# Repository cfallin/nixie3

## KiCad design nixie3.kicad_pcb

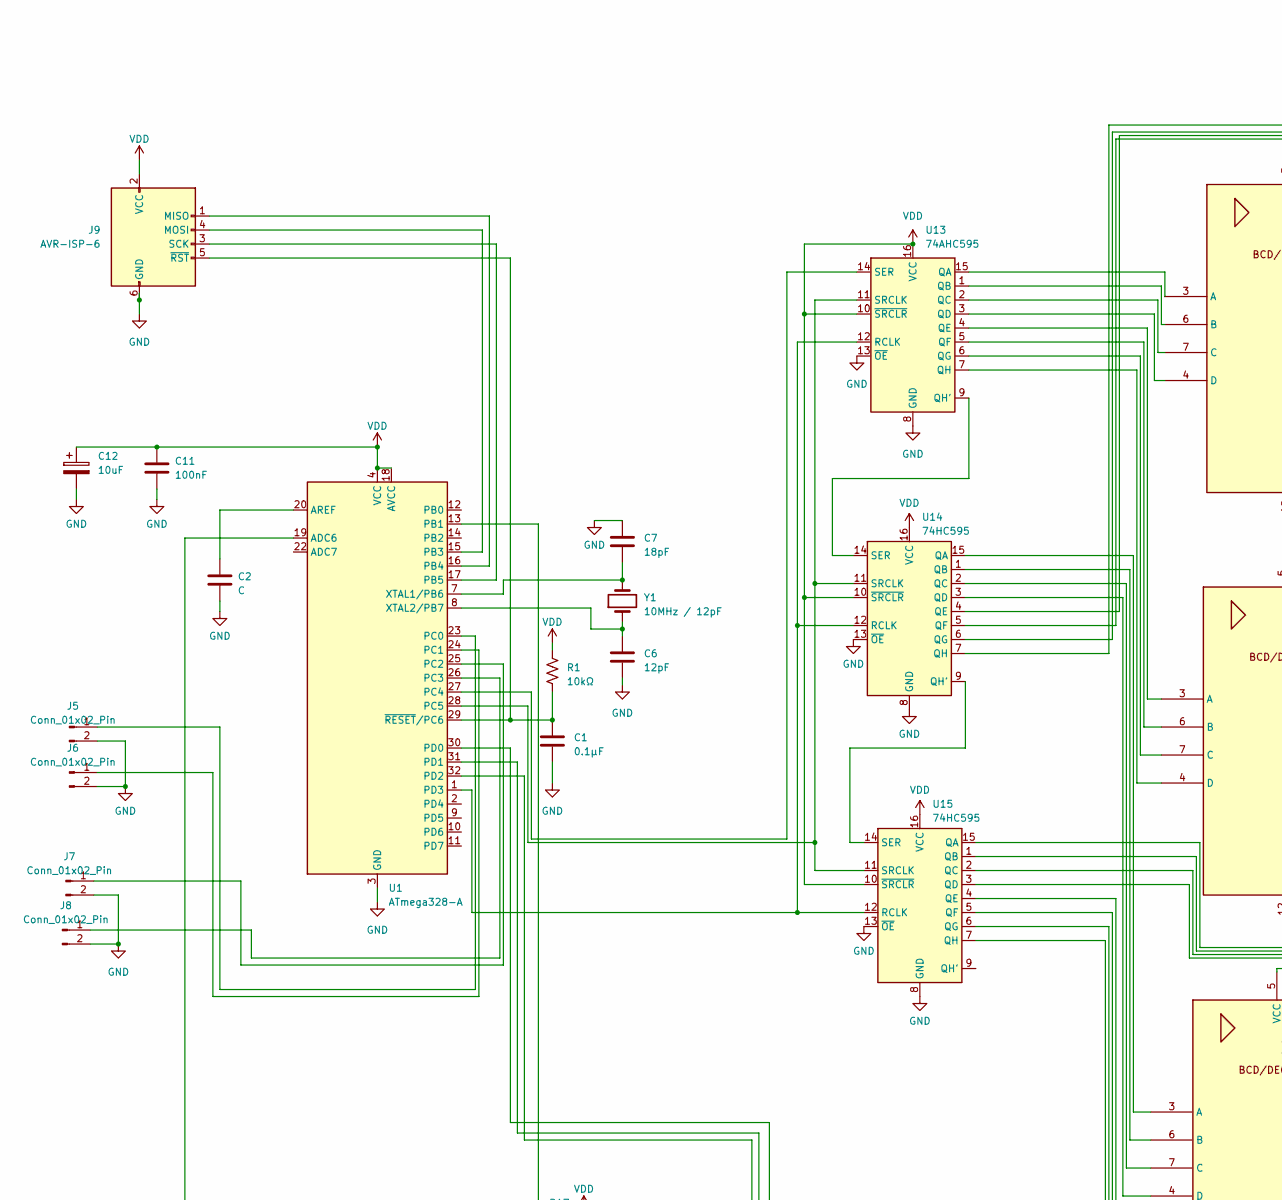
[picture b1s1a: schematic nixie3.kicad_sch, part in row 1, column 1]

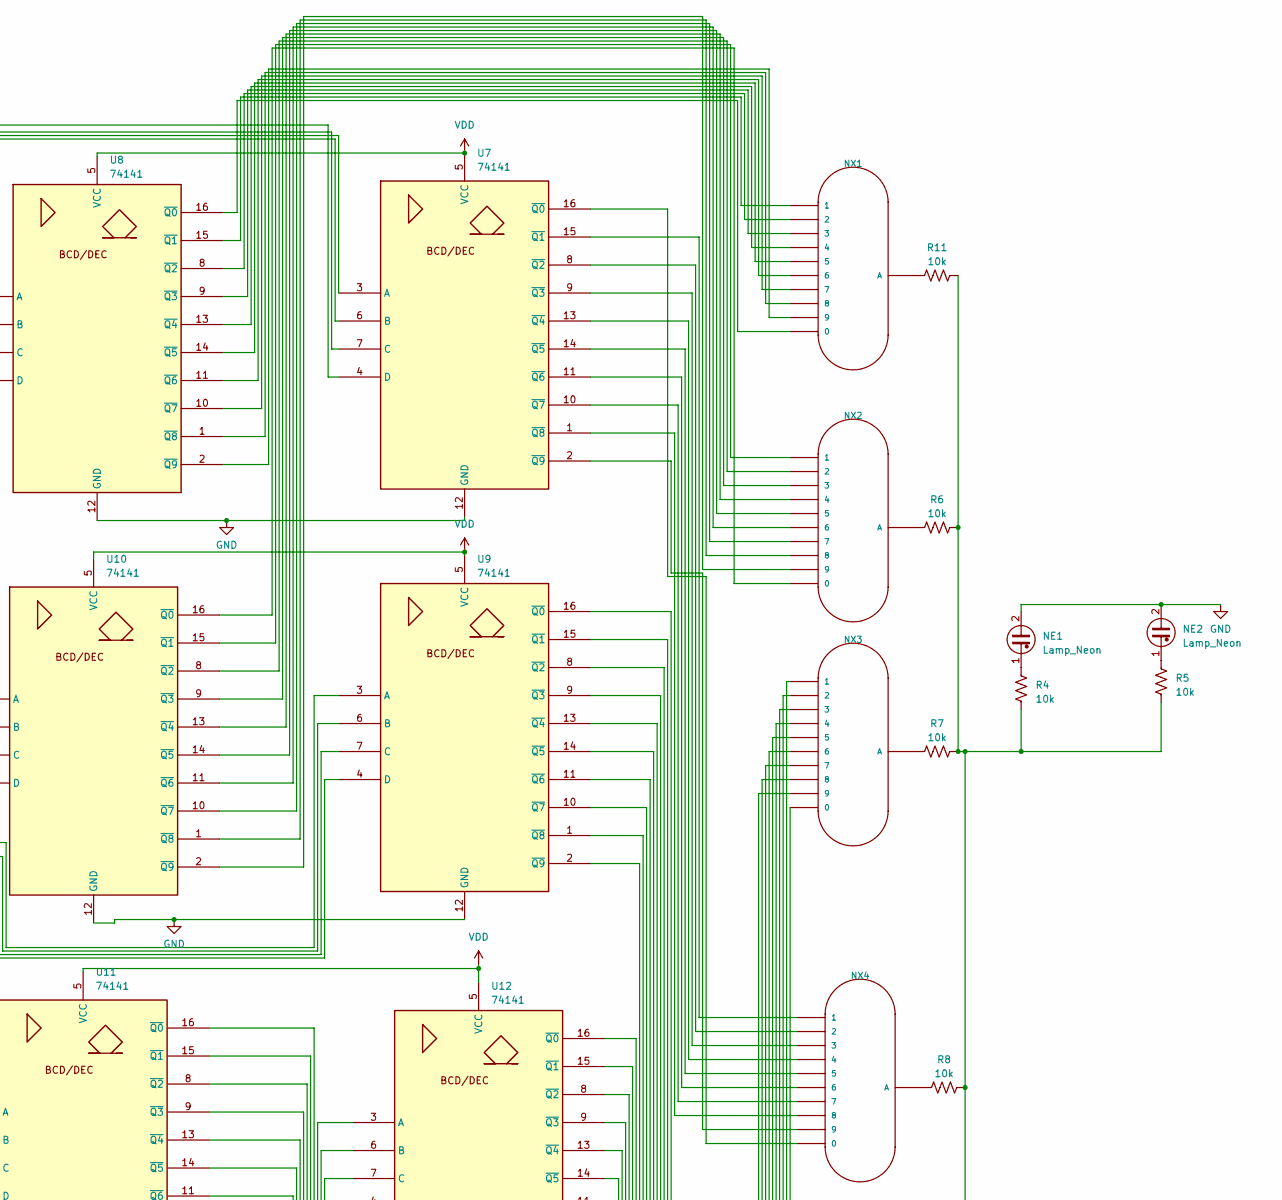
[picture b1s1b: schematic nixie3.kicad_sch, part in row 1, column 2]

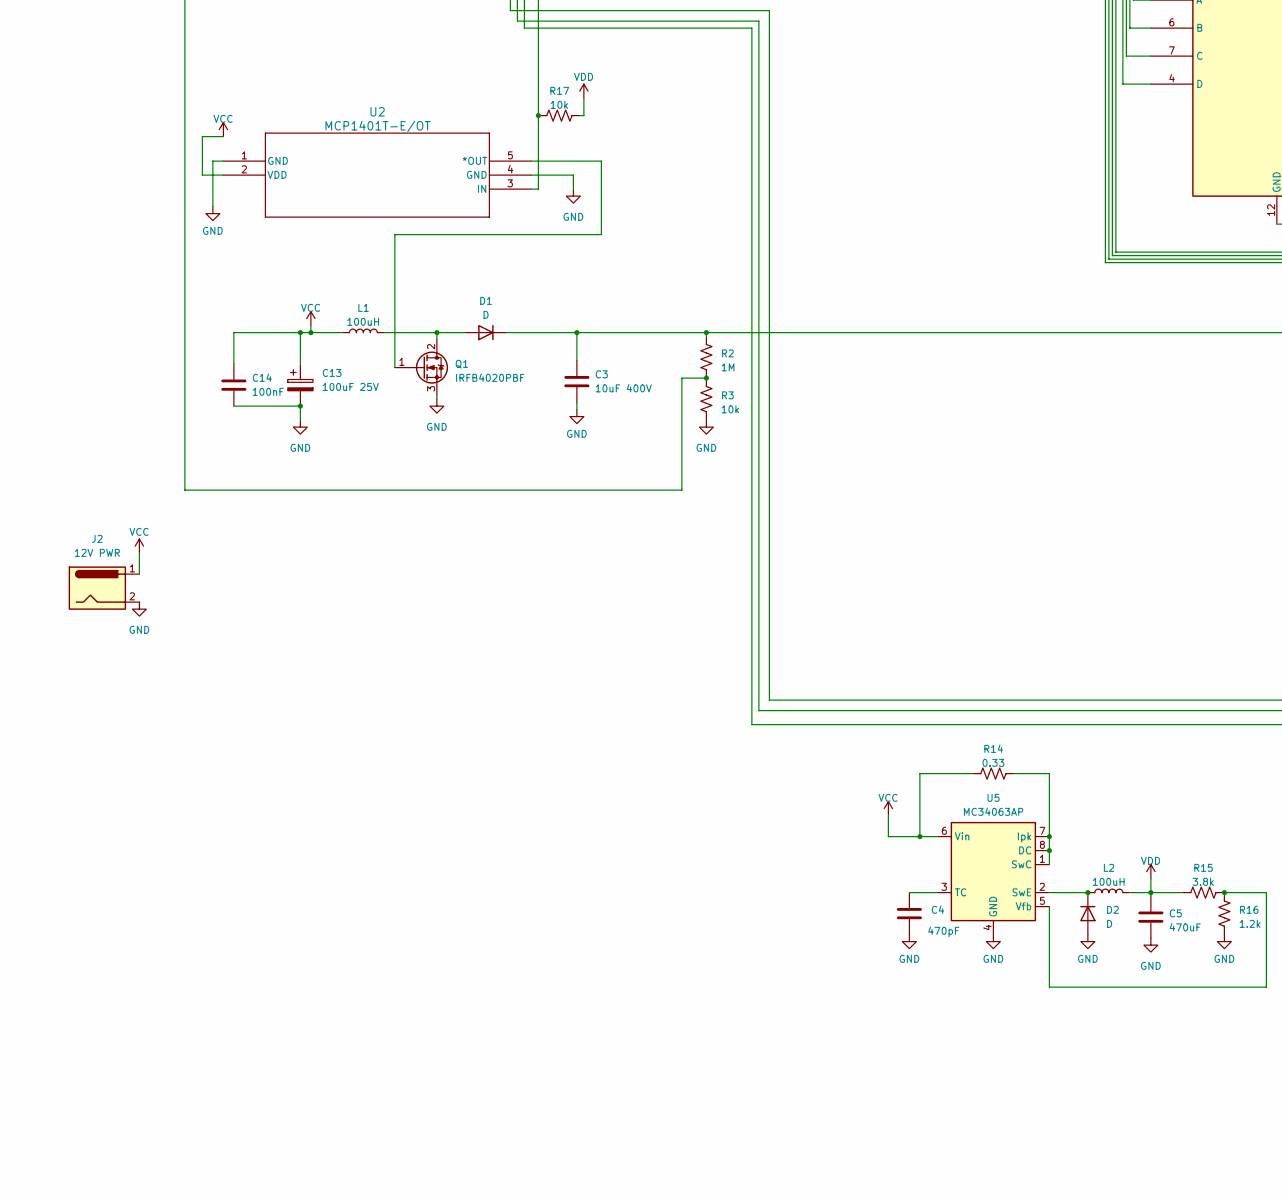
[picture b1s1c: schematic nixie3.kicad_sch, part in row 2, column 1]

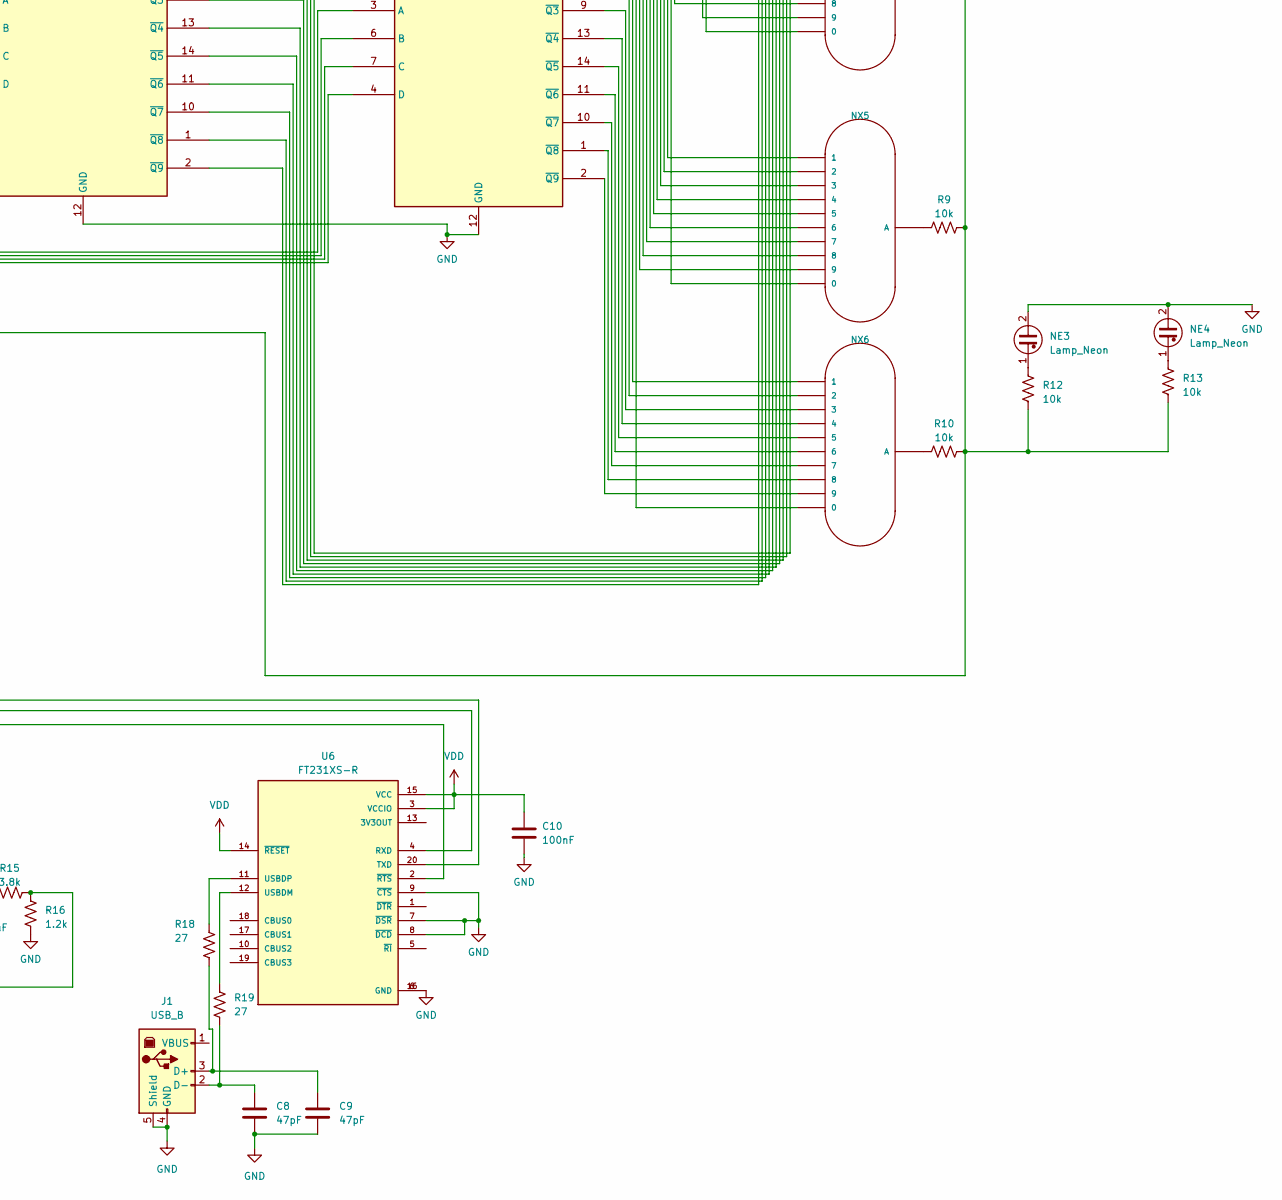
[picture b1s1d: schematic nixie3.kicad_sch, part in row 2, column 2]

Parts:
C1: 0.1µF; CP_Radial_D4.0mm_P1.50mm
C2: C; CP_Radial_D4.0mm_P1.50mm
C3: 10uF 400V; CP_Radial_D8.0mm_P5.00mm
C4: 470pF; C_Disc_D6.0mm_W2.5mm_P5.00mm
C5: 470uF; CP_Radial_D8.0mm_P5.00mm
C6: 12pF; C_Disc_D5.0mm_W2.5mm_P5.00mm
C7: 18pF; C_Disc_D5.0mm_W2.5mm_P5.00mm
C8, C9: 47pF; CP_Radial_D5.0mm_P2.50mm
C10, C11, C14: 100nF; CP_Radial_D5.0mm_P2.50mm
C12: 10uF; CP_Radial_D5.0mm_P2.50mm
C13: 100uF 25V; CP_Radial_D8.0mm_P5.00mm
D1, D2: D; D_DO-15_P12.70mm_Horizontal
J1: USB_B; USB_B_OST_USB-B1HSxx_Horizontal
J2: 12V PWR; BarrelJack_Horizontal
J5, J6, J7, J8: Conn_01x02_Pin; PinHeader_1x02_P2.54mm_Vertical
J9: AVR-ISP-6; PinHeader_2x03_P2.54mm_Vertical
L1, L2: 100uH; L_Toroid_Vertical_L16.0mm_W8.0mm_P7.62mm
NE1, NE2, NE3, NE4: Lamp_Neon; LED_D3.0mm
NX1, NX2, NX3, NX4, NX5, NX6: IN-12A; nixies-us-IN-12
Q1: IRFB4020PBF; TO-220-3_Vertical
R1: 10kΩ; R_Axial_DIN0204_L3.6mm_D1.6mm_P1.90mm_Vertical
R2: 1M; R_Axial_DIN0207_L6.3mm_D2.5mm_P2.54mm_Vertical
R3, R4, R5, R6, R7, R8, R9, R10, R11, R12, R13, R17: 10k; R_Axial_DIN0207_L6.3mm_D2.5mm_P2.54mm_Vertical
R14: 0.33; R_Axial_DIN0207_L6.3mm_D2.5mm_P2.54mm_Vertical
R15: 3.8k; R_Axial_DIN0207_L6.3mm_D2.5mm_P2.54mm_Vertical
R16: 1.2k; R_Axial_DIN0207_L6.3mm_D2.5mm_P2.54mm_Vertical
R18, R19: 27; R_Axial_DIN0204_L3.6mm_D1.6mm_P2.54mm_Vertical
U1: ATmega328-A; TQFP-32_7x7mm_P0.8mm
U2: MCP1401T-E/OT; SOT-23-5_MC_MCH
U5: MC34063AP; DIP-8_W7.62mm
U6: FT231XS-R; SOP63P599X175-20N; PARTREV 1.2; DigiKey_Part_Number 768-1129-2-ND
U7, U8, U9, U10, U11, U12: 74141; DIP-16_W7.62mm
U13: 74AHC595; DIP-16_W7.62mm
U14, U15: 74HC595; DIP-16_W7.62mm
Y1: 10MHz / 12pF; Crystal_HC49-U_Vertical

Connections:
GND: C1.2, C2.2, C3.2, C4.2, C5.2, C6.1, C7.1, C8.2, C9.2, C10.2, C11.2, C12.2, C13.2, C14.2, D2.2 (A), J1.4 (GND), J1.5 (Shield), J2.2, J5.2, J6.2, J7.2, J8.2, J9.6 (GND), NE1.2, NE2.2, NE3.2, NE4.2, Q1.3 (S), R3.2, R16.2, U1.3 (GND), U1.5 (GND), U1.21 (GND), U2.1 (GND), U2.4 (GND), U5.4 (GND), U6.6 (GND), U6.7 (~DSR), U6.8 (~DCD), U6.9 (~CTS), U6.16 (GND), U7.12 (GND), U8.12 (GND), U9.12 (GND), U10.12 (GND), U11.12 (GND), U12.12 (GND), U13.8 (GND), U13.13 (~OE), U14.8 (GND), U14.13 (~OE), U15.8 (GND), U15.13 (~OE)
unnamed: D1.2 (A), L1.2, Q1.2 (D)
unnamed: C3.1, D1.1 (K), R2.1, R4.1, R5.2, R6.2, R7.2, R8.2, R9.2, R10.2, R11.2, R12.2, R13.2
unnamed: D2.1 (K), L2.1, U5.2 (SwE)
unnamed: C9.1, J1.3 (D+), R18.2
unnamed: C8.1, J1.2 (D-), R19.2
unnamed: J5.1, U1.23 (PC0)
unnamed: J6.1, U1.24 (PC1)
unnamed: J7.1, U1.25 (PC2)
unnamed: J8.1, U1.26 (PC3)
unnamed: J9.1 (MISO), U1.16 (PB4)
unnamed: J9.4 (MOSI), U1.15 (PB3)
unnamed: J9.3 (SCK), U1.17 (PB5)
unnamed: C1.1, J9.5 (~RST), R1.2, U1.29 (~RESET/PC6)
unnamed: NE1.1, R4.2
unnamed: NE2.1, R5.1
unnamed: NE3.1, R12.1
unnamed: NE4.1, R13.1
unnamed: NX1.A, R11.1
unnamed: NX2.A, R6.1
unnamed: NX3.A, R7.1
unnamed: NX4.A, R8.1
unnamed: NX5.A, R9.1
unnamed: NX6.A, R10.1
unnamed: Q1.1 (G), U2.5 (*OUT)
unnamed: R2.2, R3.1, U1.19 (ADC6)
unnamed: C2.1, U1.20 (AREF)
unnamed: R17.1, U1.13 (PB1), U2.3 (IN)
unnamed: U1.27 (PC4), U13.14 (SER)
unnamed: U1.28 (PC5), U13.11 (SRCLK), U14.11 (SRCLK), U15.11 (SRCLK)
unnamed: U1.30 (PD0), U6.20 (TXD)
unnamed: U1.31 (PD1), U6.4 (RXD)
unnamed: U1.32 (PD2), U6.2 (~RTS)
unnamed: U1.1 (PD3), U13.12 (RCLK), U14.12 (RCLK), U15.12 (RCLK)
unnamed: C7.2, U1.7 (XTAL1/PB6), Y1.2
unnamed: C6.2, U1.8 (XTAL2/PB7), Y1.1
unnamed: R14.2, U5.1 (SwC), U5.7 (Ipk), U5.8 (DC)
unnamed: C4.1, U5.3 (TC)
unnamed: R15.2, R16.1, U5.5 (Vfb)
unnamed: R19.1, U6.12 (USBDM)
unnamed: R18.1, U6.11 (USBDP)
unnamed: NX4.0, U7.16 (~Q0)
unnamed: NX4.1, U7.15 (~Q1)
unnamed: NX4.2, U7.8 (~Q2)
unnamed: NX4.3, U7.9 (~Q3)
unnamed: NX4.4, U7.13 (~Q4)
unnamed: NX4.5, U7.14 (~Q5)
unnamed: NX4.6, U7.11 (~Q6)
unnamed: NX4.7, U7.10 (~Q7)
unnamed: NX4.8, U7.1 (~Q8)
unnamed: NX4.9, U7.2 (~Q9)
unnamed: NX1.0, U8.16 (~Q0)
unnamed: NX1.1, U8.15 (~Q1)
unnamed: NX1.2, U8.8 (~Q2)
unnamed: NX1.3, U8.9 (~Q3)
unnamed: NX1.4, U8.13 (~Q4)
unnamed: NX1.5, U8.14 (~Q5)
unnamed: NX1.6, U8.11 (~Q6)
unnamed: NX1.7, U8.10 (~Q7)
unnamed: NX1.8, U8.1 (~Q8)
unnamed: NX1.9, U8.2 (~Q9)
unnamed: NX5.0, U9.16 (~Q0)
unnamed: NX5.1, U9.15 (~Q1)
unnamed: NX5.2, U9.8 (~Q2)
unnamed: NX5.3, U9.9 (~Q3)
unnamed: NX5.4, U9.13 (~Q4)
unnamed: NX5.5, U9.14 (~Q5)
unnamed: NX5.6, U9.11 (~Q6)
unnamed: NX5.7, U9.10 (~Q7)
unnamed: NX5.8, U9.1 (~Q8)
unnamed: NX5.9, U9.2 (~Q9)
unnamed: U10.3 (A), U13.4 (QE)
unnamed: U10.6 (B), U13.5 (QF)
unnamed: U10.7 (C), U13.6 (QG)
unnamed: U10.4 (D), U13.7 (QH)
unnamed: NX2.0, U10.16 (~Q0)
unnamed: NX2.1, U10.15 (~Q1)
unnamed: NX2.2, U10.8 (~Q2)
unnamed: NX2.3, U10.9 (~Q3)
unnamed: NX2.4, U10.13 (~Q4)
unnamed: NX2.5, U10.14 (~Q5)
unnamed: NX2.6, U10.11 (~Q6)
unnamed: NX2.7, U10.10 (~Q7)
unnamed: NX2.8, U10.1 (~Q8)
unnamed: NX2.9, U10.2 (~Q9)
unnamed: U11.3 (A), U14.15 (QA)
unnamed: U11.6 (B), U14.1 (QB)
unnamed: U11.7 (C), U14.2 (QC)
unnamed: U11.4 (D), U14.3 (QD)
unnamed: NX3.0, U11.16 (~Q0)
unnamed: NX3.1, U11.15 (~Q1)
unnamed: NX3.2, U11.8 (~Q2)
unnamed: NX3.3, U11.9 (~Q3)
unnamed: NX3.4, U11.13 (~Q4)
unnamed: NX3.5, U11.14 (~Q5)
unnamed: NX3.6, U11.11 (~Q6)
unnamed: NX3.7, U11.10 (~Q7)
unnamed: NX3.8, U11.1 (~Q8)
unnamed: NX3.9, U11.2 (~Q9)
unnamed: U12.3 (A), U15.4 (QE)
unnamed: U12.6 (B), U15.5 (QF)
unnamed: U12.7 (C), U15.6 (QG)
unnamed: U12.4 (D), U15.7 (QH)
unnamed: NX6.0, U12.16 (~Q0)
unnamed: NX6.1, U12.15 (~Q1)
unnamed: NX6.2, U12.8 (~Q2)
unnamed: NX6.3, U12.9 (~Q3)
unnamed: NX6.4, U12.13 (~Q4)
unnamed: NX6.5, U12.14 (~Q5)
unnamed: NX6.6, U12.11 (~Q6)
unnamed: NX6.7, U12.10 (~Q7)
unnamed: NX6.8, U12.1 (~Q8)
unnamed: NX6.9, U12.2 (~Q9)
unnamed: U8.3 (A), U13.15 (QA)
unnamed: U8.6 (B), U13.1 (QB)
unnamed: U8.7 (C), U13.2 (QC)
unnamed: U8.4 (D), U13.3 (QD)
unnamed: U13.9 (QH'), U14.14 (SER)
unnamed: U7.3 (A), U14.4 (QE)
unnamed: U7.6 (B), U14.5 (QF)
unnamed: U7.7 (C), U14.6 (QG)
unnamed: U14.9 (QH'), U15.14 (SER)
unnamed: U7.4 (D), U14.7 (QH)
unnamed: U9.3 (A), U15.15 (QA)
unnamed: U9.6 (B), U15.1 (QB)
unnamed: U9.7 (C), U15.2 (QC)
unnamed: U9.4 (D), U15.3 (QD)
VCC: C13.1, C14.1, J2.1, L1.1, R14.1, U2.2 (VDD), U5.6 (Vin)
VDD: C5.1, C10.1, C11.1, C12.1, J9.2 (VCC), L2.2, R1.1, R15.1, R17.2, U1.4 (VCC), U1.6 (VCC), U1.18 (AVCC), U6.3 (VCCIO), U6.14 (~RESET), U6.15 (VCC), U7.5 (VCC), U8.5 (VCC), U9.5 (VCC), U10.5 (VCC), U11.5 (VCC), U12.5 (VCC), U13.10 (~SRCLR), U13.16 (VCC), U14.10 (~SRCLR), U14.16 (VCC), U15.10 (~SRCLR), U15.16 (VCC)

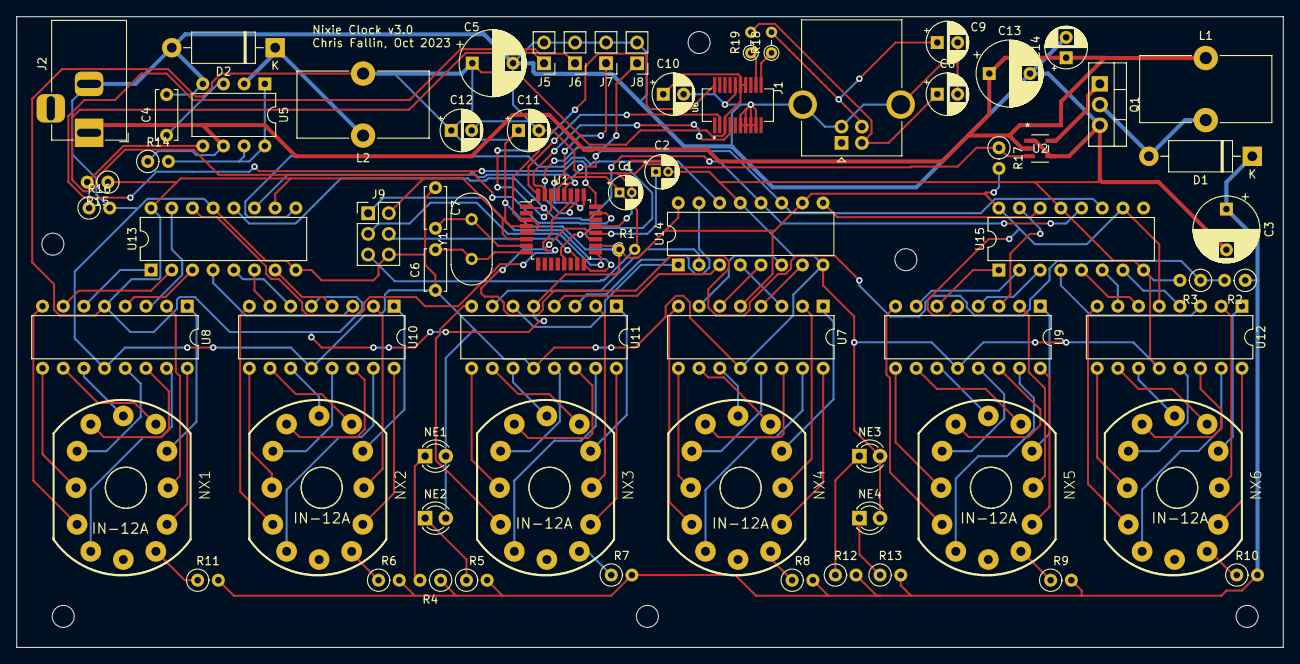
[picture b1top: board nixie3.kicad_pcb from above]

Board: 2 copper layers, 155.6 x 77.5 mm, 69 parts (0 on the bottom side), 129 nets.

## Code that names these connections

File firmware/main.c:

/*
 * Nixie Clock v3.0
 *
 * Copyright (c) 2023 Chris Fallin <chris@cfallin.org>
 * Placed under the Apache-2.0 license.
 */

/* 
 * Assume an ATmega328.
 *
 * IO connections (manufactured board version):
 *
 * PC5 is shift register clock (active high to shift).
 * PC4 is shift register data.
 * PD3 is shift register latch (active high to latch).
 *
 * Shift register output is nixie 2, 1; 4, 3; 6, 5. MSB first of BCD digits.
 *
 * PD0 is RXD from FT232 chip.
 * PD1 is TXD to FT232 chip.
 * PD2 is RTS' from FT232 chip.
 *
 * PB1 (OC1A) is out to high-voltage boost supply MOSFET driver (active low,
 * inverting driver).
 *
 * ADC6 is in from high-voltage line voltage divider (1/101 of voltage, via
 * 1M+10k divider).
 *
 * PC0 is J5 switch to ground.
 * PC1 is J6 switch to ground.
 * PC2 is J7 switch to ground.
 * PC3 is J8 switch to ground.
 *
 * Clock is 10MHz crystal, no divider.
 */

#include <avr/interrupt.h>

#include "nixie.h"

#define EXPECTED_TIMER_TICKS_PER_SEC 78125 // 20MHz / 256

long timer_ticks = 0;
long hz = EXPECTED_TIMER_TICKS_PER_SEC;
uint8_t time_h = 0, time_m = 0, time_s = 0;

#define DISPLAY_TIME 0
#define DISPLAY_SET 1
#define DISPLAY_CAL 2
int display_mode = 0;

#define UI_TIME 0
#define UI_TO_SET 1
#define UI_SET 2
#define UI_SET_NEXT 3
#define UI_SET_PLUS 4
#define UI_SET_MINUS 5

#define UI_TO_SET_CAL 6
#define UI_SET_CAL 7
#define UI_SET_CAL_NEXT 8
#define UI_SET_CAL_PLUS 9
#define UI_SET_CAL_MINUS 10
#define UI_TO_TIME 11

int ui_state = 0;
int ui_set_digit = 0;

#define BUTTON1 1
#define BUTTON2 2
#define BUTTON3 4
#define BUTTON4 8

void do_ui() {

    switch (ui_state) {
    case UI_TIME:
        display_mode = DISPLAY_TIME;
        if (switches & BUTTON1) {
            ui_state = UI_TO_SET;
        }
        break;
    case UI_TO_SET:
        display_mode = DISPLAY_TIME;
        if (!(switches & BUTTON1)) {
            ui_state = UI_SET;
            ui_set_digit = 0;
        }
        break;
    case UI_SET:
        display_mode = DISPLAY_SET;
        if (switches & BUTTON1) {
            ui_state = UI_TO_SET_CAL;
        } else if (switches & BUTTON2) {
            ui_set_digit++;
            if (ui_set_digit == 3) {
                ui_set_digit = 0;
            }
            ui_state = UI_SET_NEXT;
        } else if (switches & BUTTON3) {
            switch (ui_set_digit) {
                case 0:
                    time_h++;
                    if (time_h == 24) {
                        time_h = 0;
                    }
                    break;
                case 1:
                    time_m++;
                    if (time_m == 60) {
                        time_m = 0;
                    }
                    break;
                case 2:
                    time_s++;
                    if (time_s == 60) {
                        time_s = 0;
                    }
                    break;
            }
            ui_state = UI_SET_PLUS;
        } else if (switches & BUTTON4) {
            switch (ui_set_digit) {
                case 0:
                    if (time_h == 0) {
                        time_h = 24;
                    }
                    time_h--;
                    break;
                case 1:
                    if (time_m == 0) {
                        time_m = 60;
                    }
                    time_m--;
                    break;
                case 2:
                    if (time_s == 0) {
                        time_s = 60;
                    }
                    time_s--;
                    break;
            }
            ui_state = UI_SET_MINUS;
        }
        break;
    case UI_SET_NEXT:
        display_mode = DISPLAY_SET;
        if (!(switches & BUTTON2)) {
            ui_state = UI_SET;
        }
        break;
    case UI_SET_PLUS:
        display_mode = DISPLAY_SET;
        if (switches & BUTTON4) {
            switch (ui_set_digit) {
                case 0:
                    time_h = 0;
                    break;
                case 1:
                    time_m = 0;
                    break;
                case 2:
                    time_s = 0;
                    break;
            }
        } else if (!(switches & BUTTON3)) {
            ui_state = UI_SET;
        }
        break;
    case UI_SET_MINUS:
        display_mode = DISPLAY_SET;
        if (switches & BUTTON3) {
            switch (ui_set_digit) {
                case 0:
                    time_h = 0;
                    break;
                case 1:
                    time_m = 0;
                    break;
                case 2:
                    time_s = 0;
                    break;
            }
        } else if (!(switches & BUTTON4)) {
            ui_state = UI_SET;
        }
        break;
    case UI_TO_SET_CAL:
        display_mode = DISPLAY_SET;
        if (!(switches & BUTTON1)) {
            ui_state = UI_SET_CAL;
            ui_set_digit = 0;
        }
        break;
    case UI_SET_CAL:
        display_mode = DISPLAY_CAL;
        if (switches & BUTTON1) {
            ui_state = UI_TO_TIME;
        } else if (switches & BUTTON2) {
            ui_set_digit++;
            if (ui_set_digit == 5) {
                ui_set_digit = 0;
            }
            ui_state = UI_SET_CAL_NEXT;
        } else if (switches & BUTTON3) {
            int amt = 1;
            for (int i = 0; i < (4 - ui_set_digit); i++) {
                amt *= 10;
            }
            hz += amt;
            if (hz > 100000) {
                hz -= 100000;
            }
            ui_state = UI_SET_CAL_PLUS;
        } else if (switches & BUTTON4) {
            int amt = 1;
            for (int i = 0; i < (4 - ui_set_digit); i++) {
                amt *= 10;
            }
            hz -= amt;
            if (hz < amt) {
                hz += 100000;
            }
            ui_state = UI_SET_CAL_MINUS;
        }
        break;
    case UI_SET_CAL_NEXT:
        display_mode = DISPLAY_CAL;
        if (!(switches & BUTTON2)) {
            ui_state = UI_SET_CAL;
        }
        break;
    case UI_SET_CAL_PLUS:
        display_mode = DISPLAY_CAL;
        if (!(switches & BUTTON3)) {
            ui_state = UI_SET_CAL;
        }
        break;
    case UI_SET_CAL_MINUS:
        display_mode = DISPLAY_CAL;
        if (!(switches & BUTTON4)) {
            ui_state = UI_SET_CAL;
        }
        break;
    case UI_TO_TIME:
        display_mode = DISPLAY_CAL;
        if (!(switches & BUTTON1)) {
            ui_state = UI_TIME;
        }
        break;
    }
}

void update_display() {
    switch (display_mode) {
    case DISPLAY_TIME: {
        display_digits(time_h / 10, time_h % 10, time_m / 10, time_m % 10, time_s / 10, time_s % 10);
        break;
    }
    case DISPLAY_SET: {
        int second_half_second = timer_ticks > (hz / 2);
        int h1 = 15, h2 = 15, m1 = 15, m2 = 15, s1 = 15, s2 = 15;

        if (ui_set_digit != 0 || !second_half_second) {
            h1 = time_h / 10;
            h2 = time_h % 10;
        }
        if (ui_set_digit != 1 || !second_half_second) {
            m1 = time_m / 10;
            m2 = time_m % 10;
        }
        if (ui_set_digit != 2 || !second_half_second) {
            s1 = time_s / 10;
            s2 = time_s % 10;
        }
        display_digits(h1, h2, m1, m2, s1, s2);
        break;
    }
    case DISPLAY_CAL: {
        int second_half_second = timer_ticks > (hz / 2);
        int d1 = 15, d2 = 15, d3 = 15, d4 = 15, d5 = 15;

        if (ui_set_digit != 0 || !second_half_second) {
            d1 = (hz / 10000) % 10;
        }
        if (ui_set_digit != 1 || !second_half_second) {
            d2 = (hz / 1000) % 10;
        }
        if (ui_set_digit != 2 || !second_half_second) {
            d3 = (hz / 100) % 10;
        }
        if (ui_set_digit != 3 || !second_half_second) {
            d4 = (hz / 10) % 10;
        }
        if (ui_set_digit != 4 || !second_half_second) {
            d5 = hz % 10;
        }
        display_digits(15, d1, d2, d3, d4, d5);
    }
    }
}

int main()
{
    init_display();
    init_usart();
    init_switches();
    init_power();
    enable_timer_interrupt();
    sei();

    int pos = 0;
    int state = 0;
    while (1) {
        delay();
        read_switches();
        do_ui();
        update_display();
    }
}

void do_second() {
    time_s++;
    if (time_s == 60) {
        time_s = 0;
        time_m++;
    }
    if (time_m == 60) {
        time_m = 0;
        time_h++;
    }
    if (time_h == 24) {
        time_h = 0;
    }
}

void do_timer_int() {
    timer_ticks++;
    if (timer_ticks >= hz) {
        timer_ticks = 0;
        do_second();
    }
}

void do_serial_time(int h, int m, int s) {
    time_h = h;
    time_m = m;
    time_s = s;
    timer_ticks = 0;
}

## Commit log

2023-05-12 Initial commit.
2023-09-27 Updates.
2023-10-06 board update
2023-10-06 Changes.
2023-10-08 final board layout.
2023-10-08 final board, zip file
2023-10-08 Added final files.
2023-10-16 Initial firmware checkin.
2023-10-16 WIP.
2023-10-25 power regulation to 160V
2023-10-25 Power adjustments.
2023-10-26 Working display logic.
2023-10-27 it works
2023-10-27 Working nixieclockd serial link
2023-10-30 Update buttons.
2023-11-28 final fix.
